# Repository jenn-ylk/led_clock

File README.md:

# clock
 Code, schematics, and cad for a clock

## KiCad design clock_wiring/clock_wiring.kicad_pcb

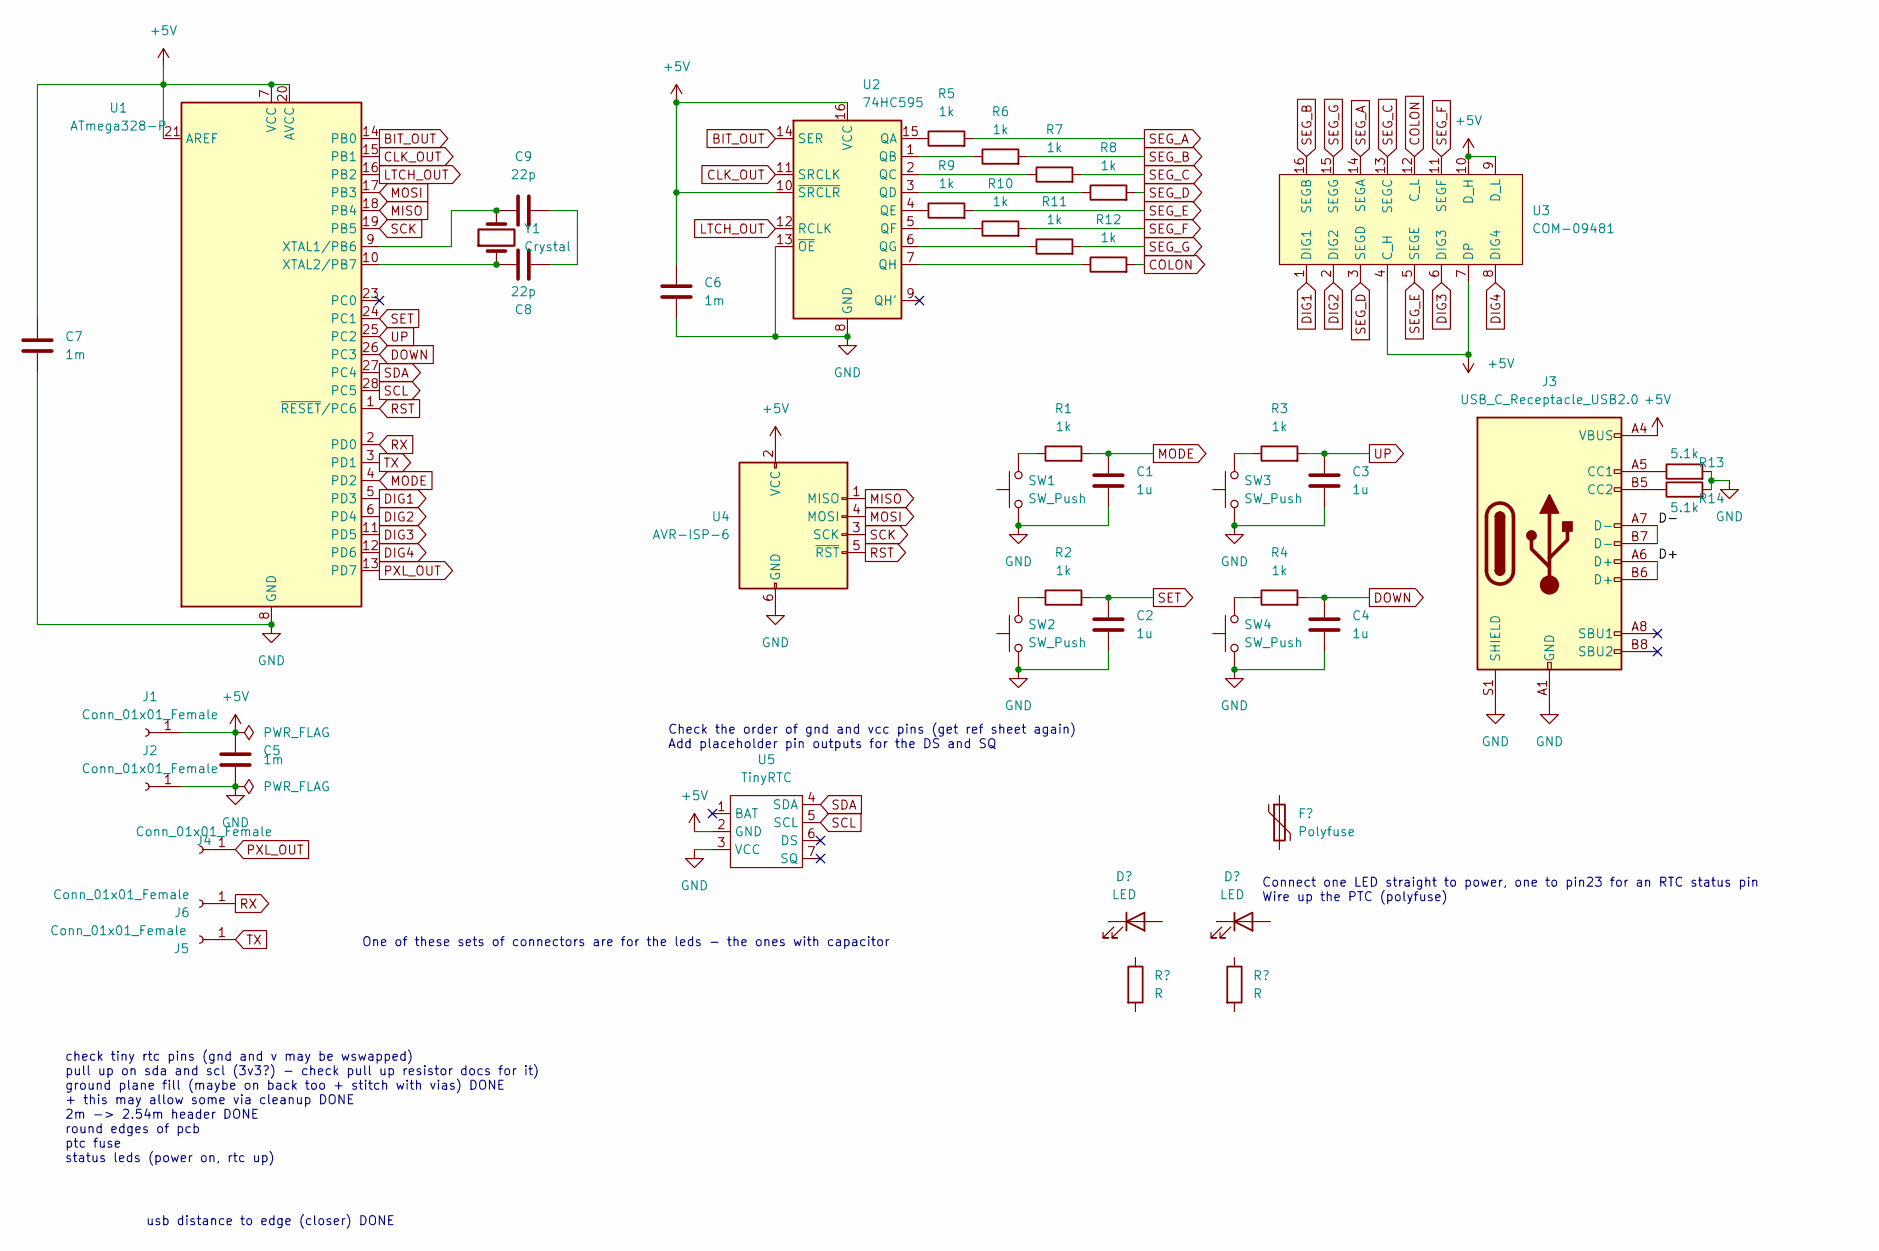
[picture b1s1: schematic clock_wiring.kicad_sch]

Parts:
C1, C2, C3, C4: 1u; C_1206_3216Metric_Pad1.33x1.80mm_HandSolder
C5, C6, C7: 1m; C_1206_3216Metric_Pad1.33x1.80mm_HandSolder
C8, C9: 22p; C_1206_3216Metric_Pad1.33x1.80mm_HandSolder
J1, J2, J4, J5, J6: Conn_01x01_Female; Pin_D1.0mm_L10.0mm_LooseFit
J3: USB_C_Receptacle_USB2.0; USB_C_Receptacle_Palconn_UTC16-G
R1, R2, R3, R4, R5, R6, R7, R8, R9, R10, R11, R12: 1k; R_1206_3216Metric_Pad1.30x1.75mm_HandSolder
R13, R14: 5.1k; R_1206_3216Metric_Pad1.30x1.75mm_HandSolder
SW1, SW2, SW3, SW4: SW_Push; SW_Tactile_Straight_KSA0Axx1LFTR
U1: ATmega328-P; DIP-28_W7.62mm_Socket
U2: 74HC595; DIP-16_W7.62mm
U3: COM-09481
U4: AVR-ISP-6; PinHeader_2x03_P2.00mm_Vertical
U5: TinyRTC
Y1: Crystal; Crystal_HC52-6mm_Vertical

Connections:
+5V: C5.1, C6.1, C7.1, J1.1, J3.A4 (VBUS), J3.A9 (VBUS), J3.B4 (VBUS), J3.B9 (VBUS), U1.7 (VCC), U1.20 (AVCC), U1.21 (AREF), U2.10 (~SRCLR), U2.16 (VCC), U3.4 (C_H), U3.7 (DP), U3.9 (D_L), U3.10 (D_H), U4.2 (VCC), U5.2 (GND)
/D+: J3.A6 (D+), J3.B6 (D+)
/D-: J3.A7 (D-), J3.B7 (D-)
BIT_OUT: U1.14 (PB0), U2.14 (SER)
CLK_OUT: U1.15 (PB1), U2.11 (SRCLK)
COLON: R12.2, U3.12 (C_L)
DIG1: U1.5 (PD3), U3.1 (DIG1)
DIG2: U1.6 (PD4), U3.2 (DIG2)
DIG3: U1.11 (PD5), U3.6 (DIG3)
DIG4: U1.12 (PD6), U3.8 (DIG4)
DOWN: C4.1, R4.2, U1.26 (PC3)
GND: C1.2, C2.2, C3.2, C4.2, C5.2, C6.2, C7.2, J2.1, J3.A1 (GND), J3.A12 (GND), J3.B1 (GND), J3.B12 (GND), J3.S1 (SHIELD), R13.2, R14.2, SW1.1, SW2.1, SW3.1, SW4.1, U1.8 (GND), U1.22 (GND), U2.8 (GND), U2.13 (~OE), U4.6 (GND), U5.3 (VCC)
LTCH_OUT: U1.16 (PB2), U2.12 (RCLK)
MISO: U1.18 (PB4), U4.1 (MISO)
MODE: C1.1, R1.2, U1.4 (PD2)
MOSI: U1.17 (PB3), U4.4 (MOSI)
unnamed: C8.1, C9.2
unnamed: C8.2, U1.10 (XTAL2/PB7), Y1.1
unnamed: C9.1, U1.9 (XTAL1/PB6), Y1.2
unnamed: J3.A5 (CC1), R13.1
unnamed: J3.B5 (CC2), R14.1
unnamed: R1.1, SW1.2
unnamed: R2.1, SW2.2
unnamed: R3.1, SW3.2
unnamed: R4.1, SW4.2
unnamed: R5.1, U2.15 (QA)
unnamed: R6.1, U2.1 (QB)
unnamed: R7.1, U2.2 (QC)
unnamed: R8.1, U2.3 (QD)
unnamed: R9.1, U2.4 (QE)
unnamed: R10.1, U2.5 (QF)
unnamed: R11.1, U2.6 (QG)
unnamed: R12.1, U2.7 (QH)
PXL_OUT: J4.1, U1.13 (PD7)
RST: U1.1 (~RESET/PC6), U4.5 (~RST)
RX: J6.1, U1.2 (PD0)
SCK: U1.19 (PB5), U4.3 (SCK)
SCL: U1.28 (PC5), U5.5 (SCL)
SDA: U1.27 (PC4), U5.4 (SDA)
SEG_A: R5.2, U3.14 (SEGA)
SEG_B: R6.2, U3.16 (SEGB)
SEG_C: R7.2, U3.13 (SEGC)
SEG_D: R8.2, U3.3 (SEGD)
SEG_E: R9.2, U3.5 (SEGE)
SEG_F: R10.2, U3.11 (SEGF)
SEG_G: R11.2, U3.15 (SEGG)
SET: C2.1, R2.2, U1.24 (PC1)
TX: J5.1, U1.3 (PD1)
UP: C3.1, R3.2, U1.25 (PC2)

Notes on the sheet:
usb distance to edge (closer) DONE
Check the order of gnd and vcc pins (get ref sheet again) Add placeholder pin outputs for the DS and SQ
One of these sets of connectors are for the leds - the ones with capacitor
Connect one LED straight to power, one to pin23 for an RTC status pin Wire up the PTC (polyfuse)
check tiny rtc pins (gnd and v may be wswapped) pull up on sda and scl (3v3?) - check pull up resistor docs for it) ground plane fill (maybe on back too + stitch with vias) DONE + this may allow some via cleanup DONE 2m -> 2.54m header DONE round edges of pcb ptc fuse status leds (power on, rtc up)

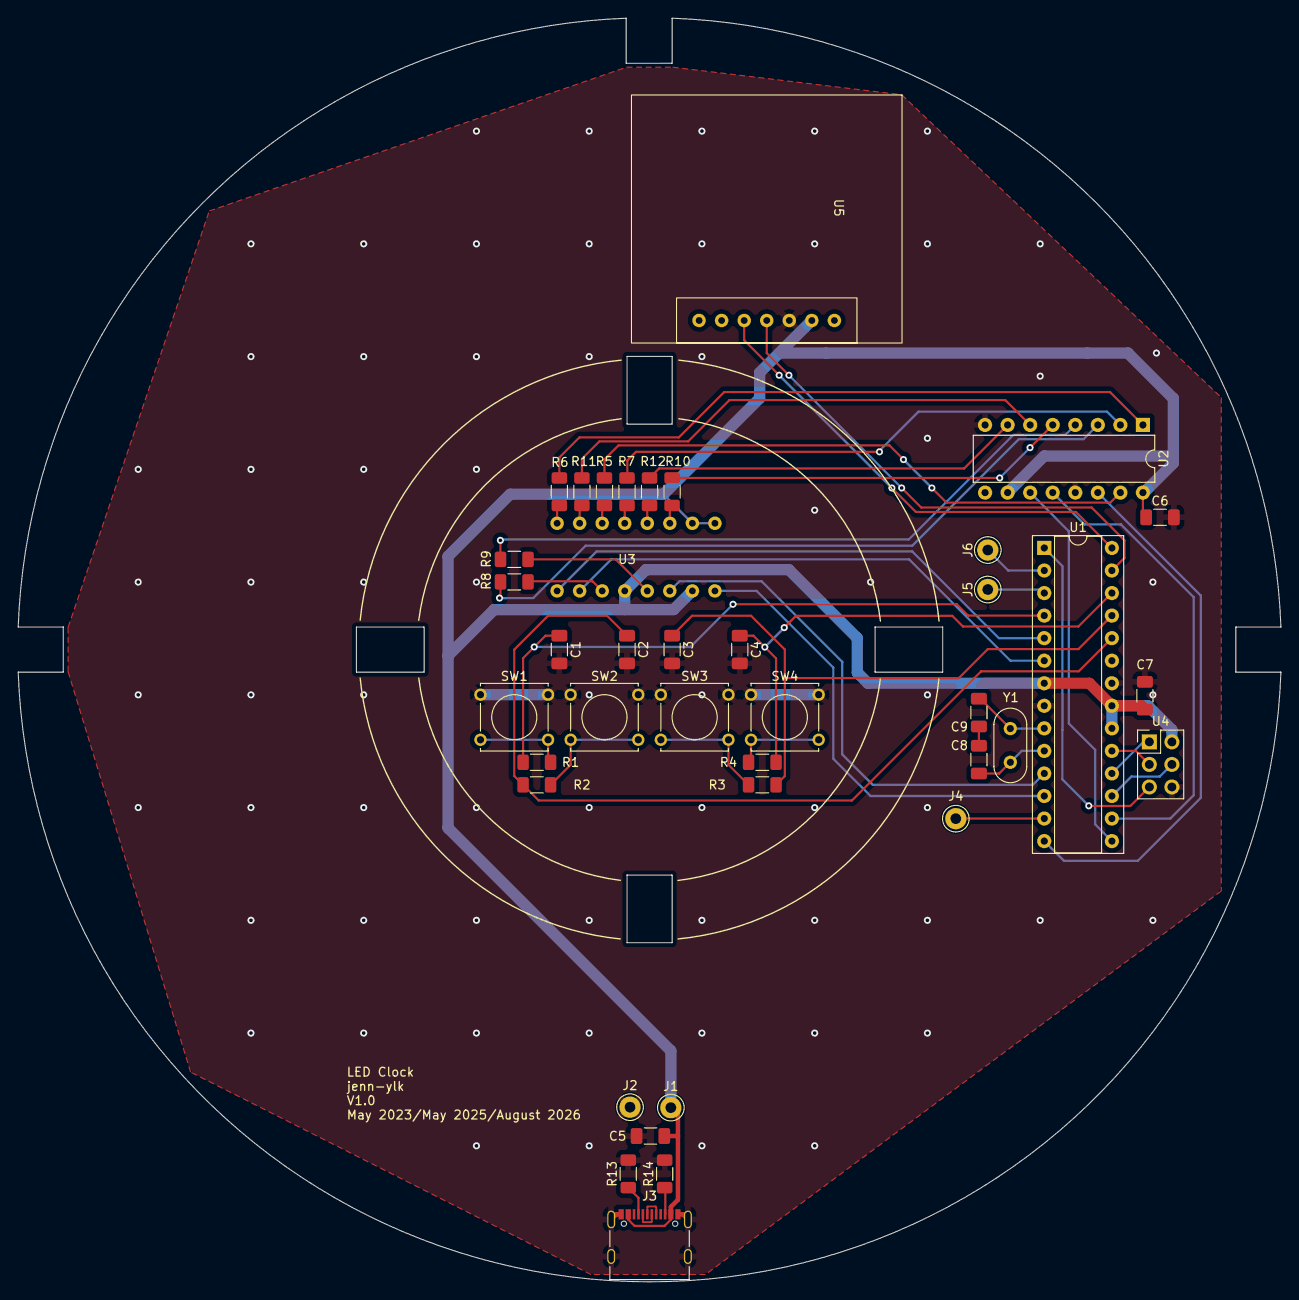
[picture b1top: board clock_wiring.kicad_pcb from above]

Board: 2 copper layers, 142.2 x 142.3 mm, 39 parts (0 on the bottom side), 49 nets.

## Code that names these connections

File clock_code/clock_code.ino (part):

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#define CLOCK_PIN 9
#define LATCH_PIN 10
// - digit pins
#define DIG1_PIN  3
#define DIG2_PIN  4
#define DIG3_PIN  5
#define DIG4_PIN  6
// - button pins
#define MODE_PIN  2
#define SET_PIN   A1
#define UP_PIN    A2
#define DOWN_PIN  A3

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    rtc.adjust(DateTime(F(__DATE__), F(__TIME__)));
  }
  now = rtc.now();
  // set up 7 segment display pins (digits + bit shifter)
  pinMode(DATA_PIN, OUTPUT);
  pinMode(CLOCK_PIN, OUTPUT);
  pinMode(LATCH_PIN, OUTPUT);
  pinMode(DIG1_PIN, OUTPUT);
  pinMode(DIG2_PIN, OUTPUT);
  pinMode(DIG3_PIN, OUTPUT);
  pinMode(DIG4_PIN, OUTPUT);
  // button setup (pullup so a "low" means the button is pressed)
  pinMode(MODE_PIN, INPUT_PULLUP);
  attachInterrupt(digitalPinToInterrupt(MODE_PIN), switch_wake, FALLING);
  pinMode(SET_PIN, INPUT_PULLUP);
  pinMode(UP_PIN, INPUT_PULLUP);
  pinMode(DOWN_PIN, INPUT_PULLUP);

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  // neopixels and 7 seg
  disp_time();

  bool set = (digitalRead(SET_PIN) == LOW);
  bool up = (digitalRead(UP_PIN) == LOW);
  bool down = (digitalRead(DOWN_PIN) == LOW);
  if (set && !previous_set) {
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
void disp_hour(int hour) {
  if (clock_mode == SLEEP) return;
  disp_digit(hour / 10, DIG1_PIN);
  disp_digit(hour % 10, DIG2_PIN);
}

void disp_minute(int minute) {
  if (clock_mode == SLEEP) return;
  disp_digit(minute / 10, DIG3_PIN);
  disp_digit(minute % 10, DIG4_PIN);
}

void disp_digit(int digit, int pin) {
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
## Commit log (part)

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2022-09-02 initial commit of code and schematic
2022-09-02 added 12 hour rollover, moving some things into functions
2022-09-06 updates to 7seg writing, added buttons to schematic (researching mic output voltages)
2022-10-20 start of neopix code
2022-10-30 added pixel display and button code to test
2022-11-04 button functionality, confirmed clock hand movement
2023-01-03 changed timekeeping to use RTC
2023-01-07 switched to rtc usage rather than internal clock, partial mode button changes, schematic updates and mic removal
2026-03-14 some more pcb progress before adding layout + maybe power circuit change
